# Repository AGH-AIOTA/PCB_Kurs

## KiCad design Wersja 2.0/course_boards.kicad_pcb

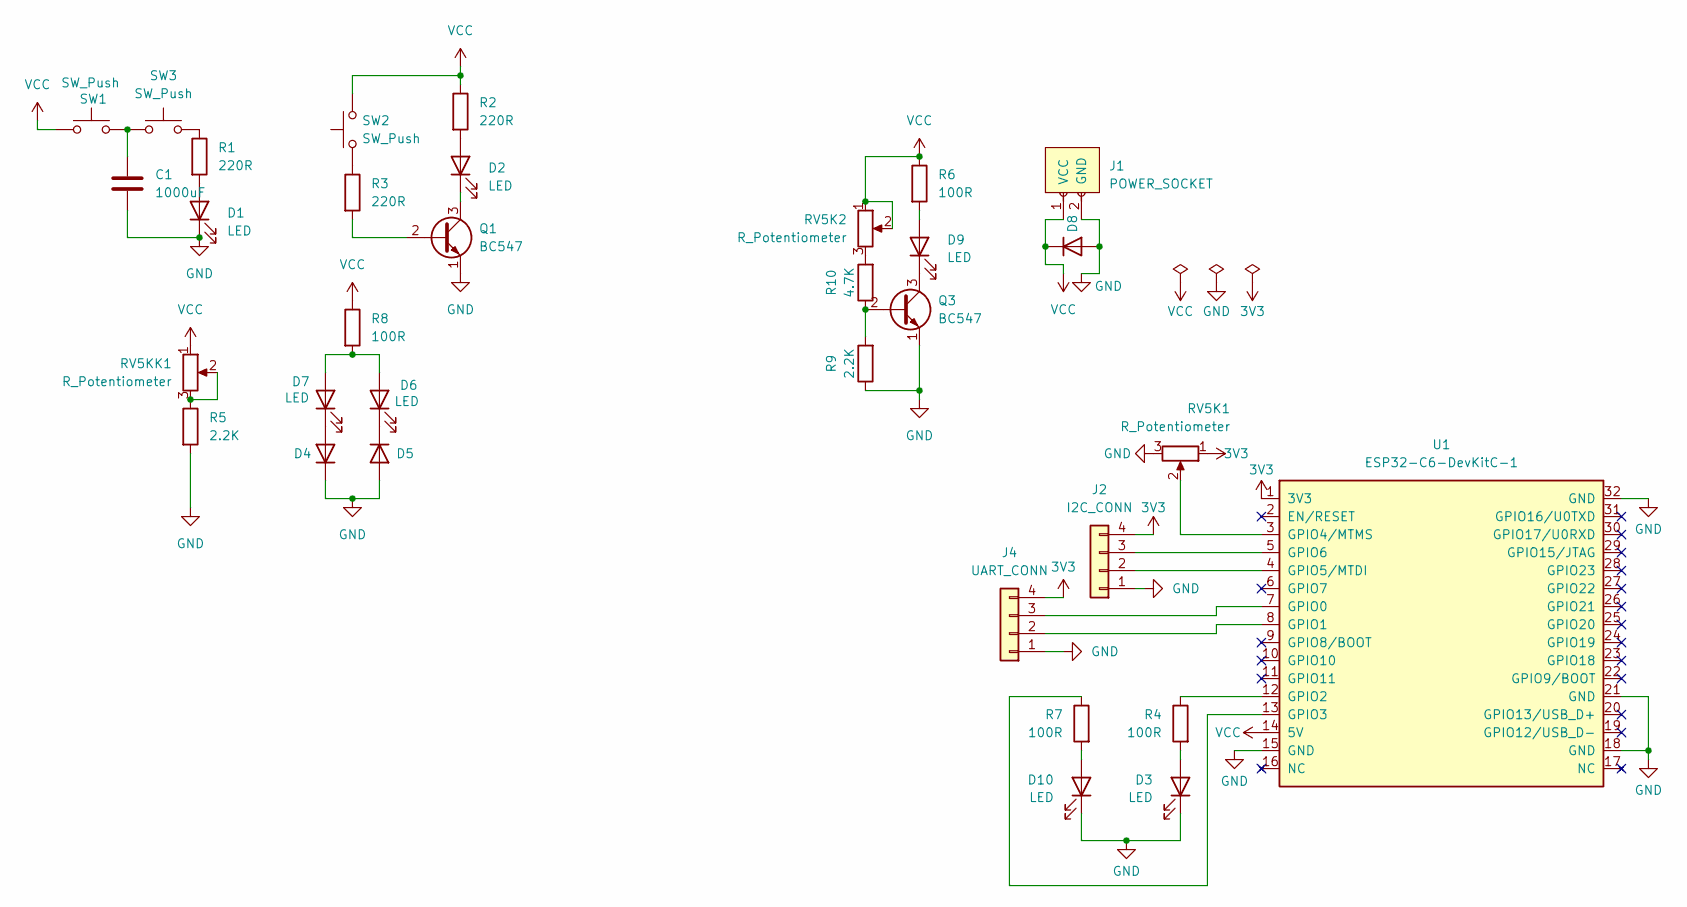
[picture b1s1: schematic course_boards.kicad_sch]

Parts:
C1: 1000uF; CP_Radial_D10.0mm_P5.00mm
D1, D2, D3, D6, D7, D9, D10: LED; LED_D5.0mm
D4, D5: 1N4148WT; D_A-405_P7.62mm_Horizontal
D8: 1N4148WT; D_5W_P12.70mm_Horizontal
J1: POWER_SOCKET; TerminalBlock_bornier-2_P5.08mm
J2: I2C_CONN; PinHeader_1x04_P2.54mm_Vertical
J4: UART_CONN; PinHeader_1x04_P2.54mm_Vertical
Q1, Q3: BC547; TO-92L_Wide
R1, R2, R3: 220R; R_Axial_DIN0207_L6.3mm_D2.5mm_P7.62mm_Horizontal
R4, R6, R7, R8: 100R; R_Axial_DIN0207_L6.3mm_D2.5mm_P7.62mm_Horizontal
R5, R9: 2.2K; R_Axial_DIN0207_L6.3mm_D2.5mm_P7.62mm_Horizontal
R10: 4.7K; R_Axial_DIN0207_L6.3mm_D2.5mm_P7.62mm_Horizontal
RV5K1, RV5K2, RV5KK1: R_Potentiometer; Potentiometer_Alps_RK163_Single_Horizontal
SW1, SW2, SW3: SW_Push; SW_PUSH_6mm
U1: ESP32-C6-DevKitC-1

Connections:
3V3: J2.4, J4.4, RV5K1.1, U1.1 (3V3)
GND: C1.2, D1.1 (K), D3.1 (K), D4.1 (K), D5.2 (A), D8.2 (A), D10.1 (K), J1.2 (GND), J2.1, J4.1, Q1.1 (E), Q3.1 (E), R5.2, R9.1, RV5K1.3, U1.15 (GND), U1.18 (GND), U1.21 (GND), U1.32 (GND)
unnamed: C1.1, SW1.2, SW3.1
unnamed: D1.2 (A), R1.2
unnamed: D2.2 (A), R2.2
unnamed: D2.1 (K), Q1.3 (C)
unnamed: D3.2 (A), R4.2
unnamed: D4.2 (A), D6.1 (K)
unnamed: D5.1 (K), D7.1 (K)
unnamed: D6.2 (A), D7.2 (A), R8.2
unnamed: D9.2 (A), R6.2
unnamed: D9.1 (K), Q3.3 (C)
unnamed: D10.2 (A), R7.2
unnamed: J2.2, U1.4 (GPIO5/MTDI)
unnamed: J2.3, U1.5 (GPIO6)
unnamed: J4.2, U1.8 (GPIO1)
unnamed: J4.3, U1.7 (GPIO0)
unnamed: Q1.2 (B), R3.2
unnamed: Q3.2 (B), R9.2, R10.1
unnamed: R1.1, SW3.2
unnamed: R3.1, SW2.1
unnamed: R5.1, RV5KK1.2, RV5KK1.3
unnamed: R10.2, RV5K2.3
unnamed: R4.1, U1.12 (GPIO2)
unnamed: R7.1, U1.13 (GPIO3)
unnamed: RV5K1.2, U1.3 (GPIO4/MTMS)
VCC: D8.1 (K), J1.1 (VCC), R2.1, R6.1, R8.1, RV5K2.1, RV5K2.2, RV5KK1.1, SW1.1, SW2.2, U1.14 (5V)

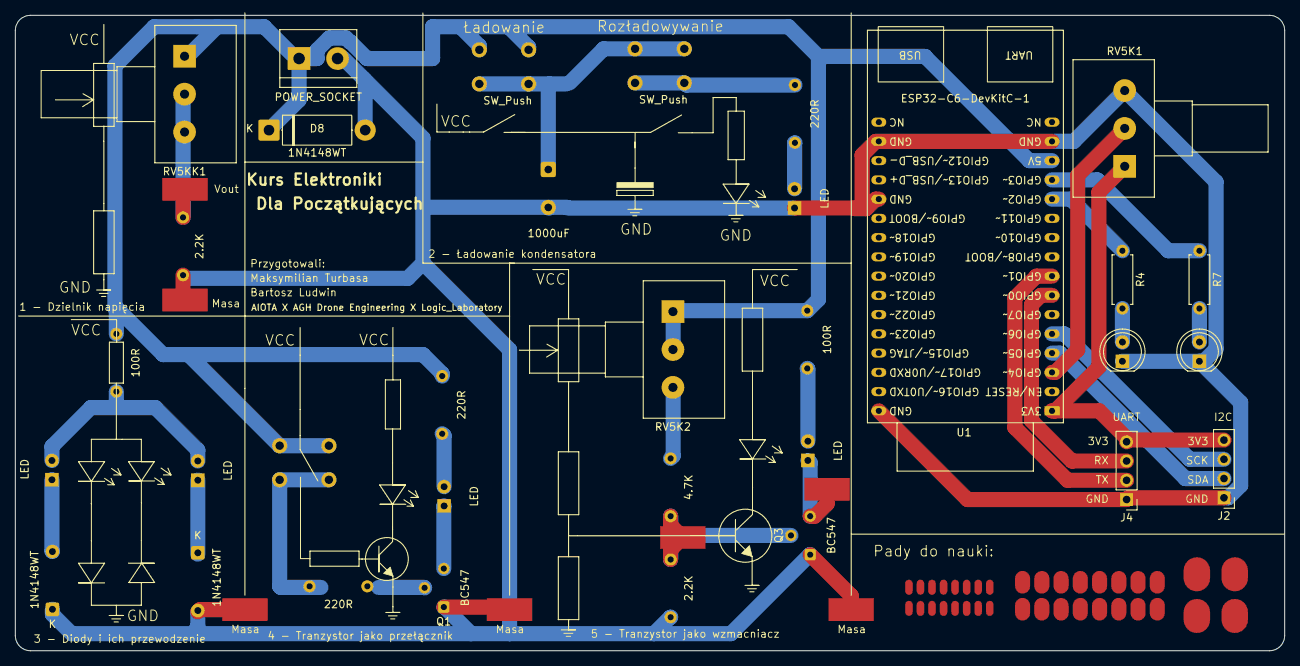
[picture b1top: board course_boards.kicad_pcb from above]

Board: 2 copper layers, 167.5 x 83.8 mm, 33 parts (0 on the bottom side), 27 nets.

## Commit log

2026-04-07 upload files
2026-04-07 fix ver 2
2026-04-07 add more space in esp section
2026-04-07 add drone logo
2026-04-07 add gerbers
2026-04-09 fix typo
2026-04-09 v2.3
2026-04-09 more pads!
2026-05-12 relocate components in schematic
2026-05-12 add microcontroller part
2026-05-12 feat: add educational script for ESP32-C6 microcontroller programming basics
2026-05-12 Deployed faa3d82 with MkDocs version: 1.6.1
2026-05-12 chore: add internationalization support and site assets for documentation project
2026-05-12 Deployed 6366023 with MkDocs version: 1.6.1
2026-05-12 feat: initialize documentation site structure and add initial markdown content
2026-05-12 small fixes
2026-05-13 Deployed d262672 with MkDocs version: 1.6.1
2026-05-13 done
2026-05-13 Deployed 4295690 with MkDocs version: 1.6.1
2026-05-13 deploy
2026-05-13 Deployed 957399a with MkDocs version: 1.6.1
2026-05-13 change to correct author
2026-05-13 fix rendering
2026-05-13 Deployed bedd803 with MkDocs version: 1.6.1
2026-05-13 deploy final version
2026-05-13 Deployed aa17b13 with MkDocs version: 1.6.1
2026-05-13 feat: add course documentation for ESP32-C6 microcontroller programming exercises
2026-05-13 Rename teoria_wstep.txt to teoria_wstep.md
2026-05-13 Deployed ac606b5 with MkDocs version: 1.6.1
2026-05-13 feat: add course content for microcontroller programming and update search index
2026-05-13 Deployed 1621ac6 with MkDocs version: 1.6.1
2026-05-13 fix code
2026-05-13 Deployed 89a3a93 with MkDocs version: 1.6.1
2026-05-13 Deployed 6f2fff1 with MkDocs version: 1.6.1
2026-05-13 feat: add comprehensive ESP32-C6 programming tutorial and course materials
2026-05-13 Deployed 1d845c6 with MkDocs version: 1.6.1
2026-05-13 add cnc fix
2026-05-13 Deployed 95d673a with MkDocs version: 1.6.1
2026-05-13 change image
2026-05-13 add Advanced Modules guide with FreeRTOS, Wi-Fi and BLE topics
2026-05-13 fix script
2026-05-13 refactor so it support web version
2026-05-13 Deployed b8fbc90 with MkDocs version: 1.6.1
2026-05-13 add deploy code
2026-05-13 Deployed 6d3d803 with MkDocs version: 1.6.1
2026-05-14 deployed v2
2026-05-14 Deployed 6c66bbc with MkDocs version: 1.6.1
2026-05-14 add vital info to freertos excercise
2026-05-14 Deployed fb52b4f with MkDocs version: 1.6.1
2026-05-14 finish wireless communication part
2026-05-14 Deployed b1cb0ae with MkDocs version: 1.6.1
2026-05-14 refactor structure
2026-05-14 add suggestions for future version
2026-05-14 kolejne pomysły
